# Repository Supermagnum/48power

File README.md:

# 48power
A small PCB that supplies +48 volt phantom power to a balanced audio system. It also has audio out to mono headphone.
It uses a LM51571QRTERQ1 to boost the voltage from a 9V battery to +48 V and a Hammond Manufacturing 108F Audio transformer.

Datasheet for the transformer:
https://github.com/Supermagnum/48power/blob/main/108F(1).pdf

Datasheet for LM51571QRTERQ1 in WQFN (16) package :
https://github.com/Supermagnum/48power/blob/main/lm51571-q1.pdf

Component selection according to Texas Instruments calculator:
https://raw.githubusercontent.com/Supermagnum/48power/main/WBSchematicXLM5157QRTERQ1.svg

Now also with a small mono amplifier, with adjustable volume ( potentiometer ).

LM386 datasheet:
https://github.com/Supermagnum/48power/blob/main/lm386(2).pdf

Please use metal film resistors, 1% tolerance or better.
High quality capacitors, audio grade ceramic X7R or better.

All component values is on the pdf file:
https://github.com/Supermagnum/48power/blob/main/supply.pdf
There is only one SMD component.

PCB board dimensions:
https://raw.githubusercontent.com/Supermagnum/48power/main/dimentions.png

Aisler PCB:
https://aisler.net/p/QQVLMIWH

The PCB board is to be mounted inside a metal box, on metal standoffs.
Ø2mm bolts with nuts can be used.
The components on the PCB must not touch the metal box.
The XLR cable shield must be connected to the metal box.
No of the internal leads should at any time be connected to the metal box.
Use a Ø4mm cable that has shield and 3 conductors.
A 3 pin XLR connector is wired up like this: https://github.com/Supermagnum/piezo-balanced/blob/main/XLR%2BConnector%2BPinout%2BDiagram%2BRear%2BPin%2B2%2BHot%2Bv2%2Bgreen__01.jpg 

NOTE:  
The XLR 3 pin plug has a solder lug for the shield for a reason.
It is my opinion that a shielded cable with 3 conductors inside is the best.
Suggested cable: Digi-Key Part Number:30-01225-5-ND

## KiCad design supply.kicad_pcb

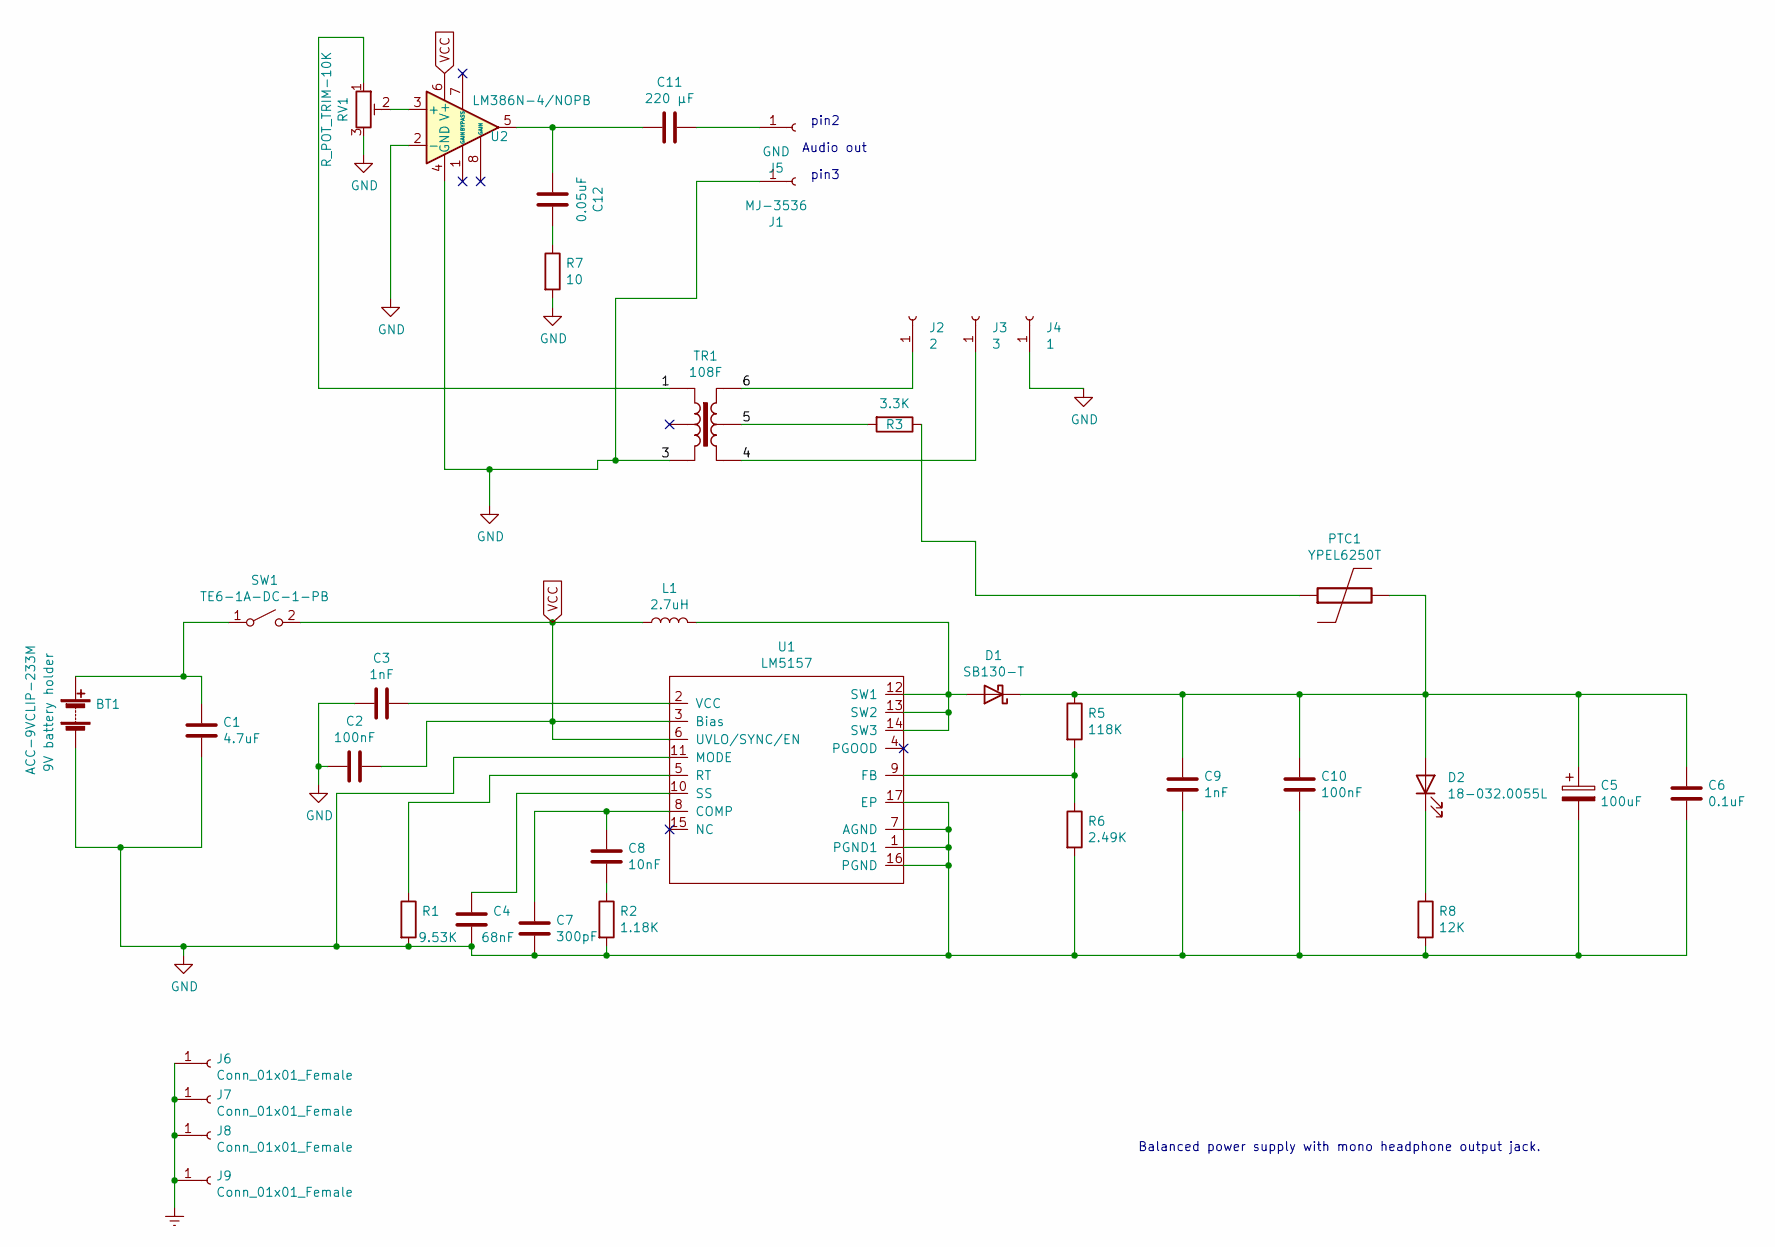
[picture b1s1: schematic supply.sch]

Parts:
BT1: ACC-9VCLIP-233M; PinHeader_1x02_P2.54mm_Vertical
C1: 4.7uF; C_Disc_D3.8mm_W2.6mm_P2.50mm
C2, C10: 100nF; C_Disc_D3.8mm_W2.6mm_P2.50mm
C3, C9: 1nF; C_Disc_D3.8mm_W2.6mm_P2.50mm
C4: 68nF; C_Disc_D3.8mm_W2.6mm_P2.50mm
C5: 100uF; CP_Radial_D8.0mm_P3.50mm
C6: 0.1uF; C_Disc_D3.8mm_W2.6mm_P2.50mm
C7: 300pF; C_Disc_D3.8mm_W2.6mm_P2.50mm
C8: 10nF; C_Disc_D3.8mm_W2.6mm_P2.50mm
C11: 220 µF; CP_Radial_D6.3mm_P2.50mm
C12: 0.05uF; C_Disc_D3.8mm_W2.6mm_P2.50mm
D1: SB130-T; D_DO-35_SOD27_P7.62mm_Horizontal
D2: 18-032.0055L; LED_D2.0mm_W4.8mm_H2.5mm_FlatTop
J1: MJ-3536; MountingHole_2.2mm_M2_DIN965_Pad
J2: 2; MountingHole_2.2mm_M2_DIN965_Pad
J3: 3; MountingHole_2.2mm_M2_DIN965_Pad
J4: 1; MountingHole_2.2mm_M2_DIN965_Pad
J5: GND; MountingHole_2.2mm_M2_DIN965_Pad
J6, J7, J8, J9: Conn_01x01_Female; MountingHole_2.2mm_M2_DIN965_Pad
L1: 2.7uH; L_Axial_L9.5mm_D4.0mm_P12.70mm_Horizontal_Fastron_SMCC
PTC1: YPEL6250T; R_Axial_DIN0204_L3.6mm_D1.6mm_P5.08mm_Horizontal
R1: 9.53K; R_Axial_DIN0207_L6.3mm_D2.5mm_P7.62mm_Horizontal
R2: 1.18K; R_Axial_DIN0207_L6.3mm_D2.5mm_P7.62mm_Horizontal
R3: 3.3K; R_Axial_DIN0207_L6.3mm_D2.5mm_P7.62mm_Horizontal
R5: 118K; R_Axial_DIN0207_L6.3mm_D2.5mm_P7.62mm_Horizontal
R6: 2.49K; R_Axial_DIN0207_L6.3mm_D2.5mm_P7.62mm_Horizontal
R7: 10; R_Axial_DIN0207_L6.3mm_D2.5mm_P7.62mm_Horizontal
R8: 12K; R_Axial_DIN0204_L3.6mm_D1.6mm_P7.62mm_Horizontal
RV1: R_POT_TRIM-10K; PinHeader_1x03_P2.54mm_Vertical
SW1: TE6-1A-DC-1-PB; PinHeader_2x01_P2.00mm_Vertical
TR1: 108F
U1: LM5157; WQFN-16_EP_3.15x3.15_Pitch0.5mm
U2: LM386N-4/NOPB; DIP-8_W7.62mm

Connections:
/1: RV1.1, TR1.1
/4: J3.1, TR1.4
/5: R3.2, TR1.5
/6: J2.1, TR1.6
Earth: J6.1, J7.1, J8.1, J9.1
GND: BT1.2 (-), C1.2, C2.2, C3.2, C4.2, C5.2, C6.1, C7.2, C9.1, C10.1, J1.1, J4.1, R1.2, R2.2, R6.2, R7.2, R8.2, RV1.3, TR1.3, U1.1 (PGND1), U1.7 (AGND), U1.11 (MODE), U1.16 (PGND), U1.17 (EP), U2.2 (-), U2.4 (GND)
unnamed: BT1.1 (+), C1.1, SW1.1 (A)
unnamed: C3.1, U1.2 (VCC)
unnamed: C4.1, U1.10 (SS)
unnamed: C7.1, C8.1, U1.8 (COMP)
unnamed: C8.2, R2.1
unnamed: C5.1, C6.2, C9.2, C10.2, D1.1 (K), D2.2 (A), PTC1.2, R5.1
unnamed: C11.1, J5.1
unnamed: C11.2, C12.2, U2.5
unnamed: C12.1, R7.1
unnamed: D1.2 (A), L1.2, U1.12 (SW1), U1.13 (SW2), U1.14 (SW3)
unnamed: D2.1 (K), R8.1
unnamed: PTC1.1, R3.1
unnamed: R1.1, U1.5 (RT)
unnamed: R5.2, R6.1, U1.9 (FB)
unnamed: RV1.2, U2.3 (+)
VCC: C2.1, L1.1, SW1.2 (B), U1.3 (Bias), U1.6 (UVLO/SYNC/EN), U2.6 (V+)

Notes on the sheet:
Balanced power supply with mono headphone output jack.
Audio out
pin2
pin3

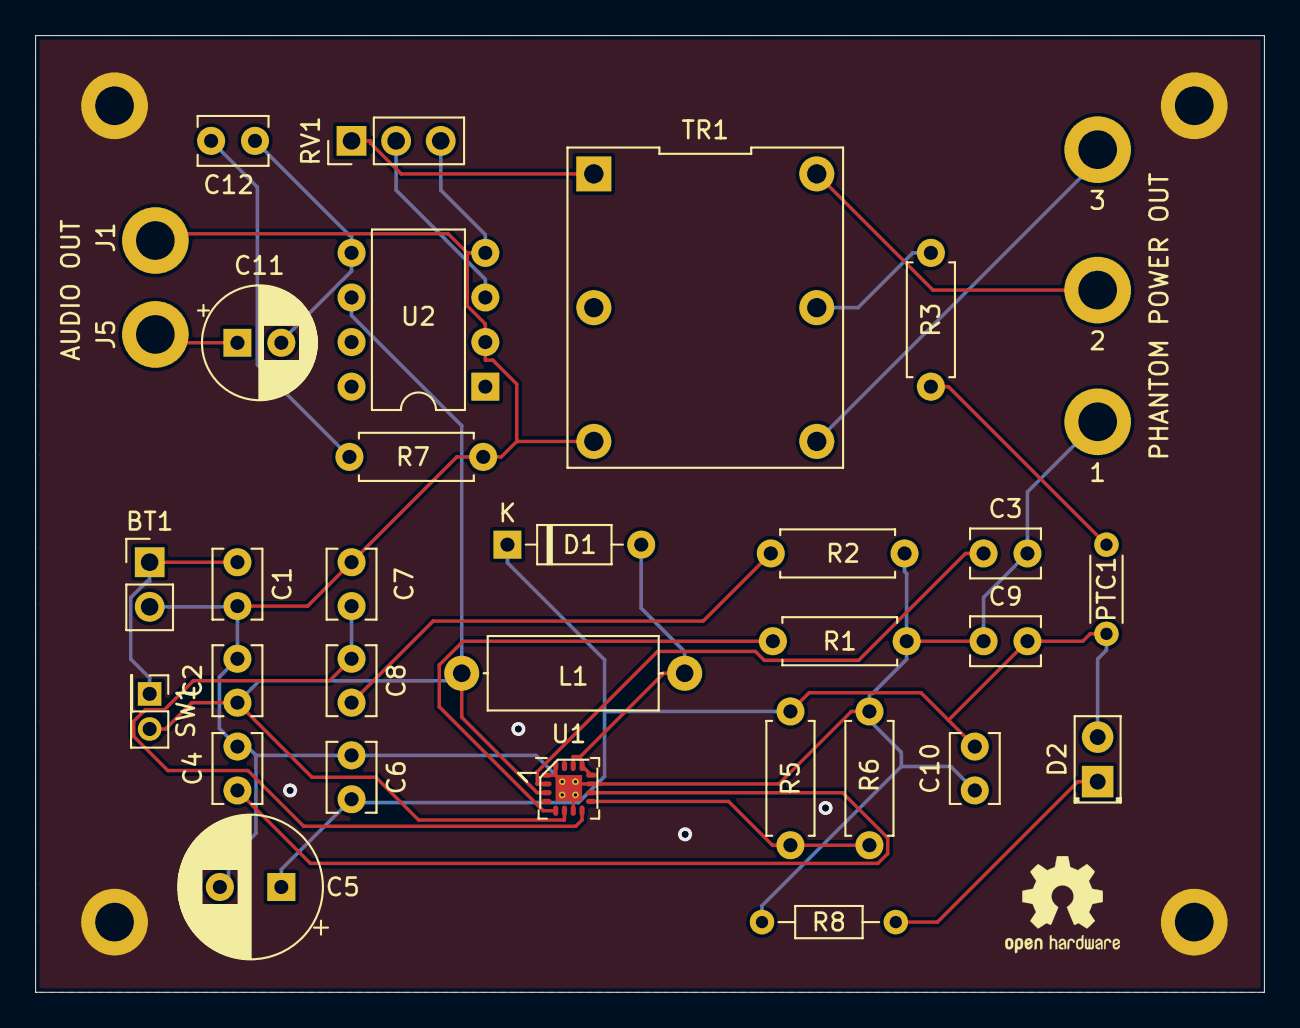
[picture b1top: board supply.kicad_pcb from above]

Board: 2 copper layers, 70.0 x 54.5 mm, 38 parts (0 on the bottom side), 22 nets.

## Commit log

2021-06-21 Add files via upload
    updated
2021-06-21 Add files via upload
    Updated files.
2021-06-22 Add files via upload
    Datasheet
2021-06-23 Add files via upload
    update, added correct diode and PCT fuse.
2021-06-23 Add files via upload
    update due to component change.
